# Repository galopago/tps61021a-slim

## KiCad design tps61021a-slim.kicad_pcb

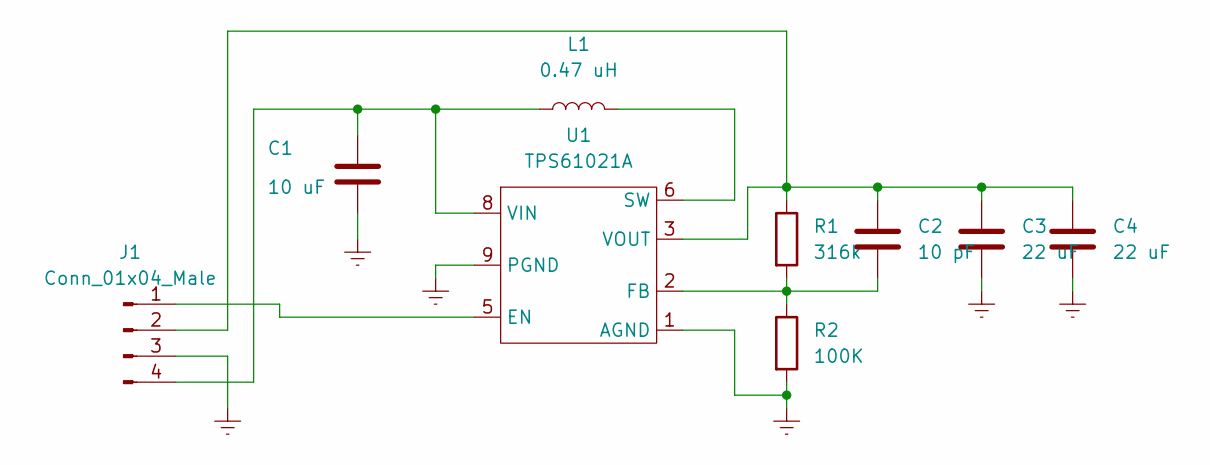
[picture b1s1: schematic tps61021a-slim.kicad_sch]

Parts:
C1: 10 uF; C_0805_2012Metric_Pad1.18x1.45mm_HandSolder
C2: 10 pF; C_0805_2012Metric_Pad1.18x1.45mm_HandSolder
C3, C4: 22 uF; C_0805_2012Metric_Pad1.18x1.45mm_HandSolder
J1: Conn_01x04_Male; PinHeader_1x04_P2.54mm_Vertical
L1: 0.47 uH; L_Ferrocore_DLG-0403
R1: 316k; R_0805_2012Metric_Pad1.20x1.40mm_HandSolder
R2: 100K; R_0805_2012Metric_Pad1.20x1.40mm_HandSolder
U1: TPS61021A; WSON-8-1EP_2x2mm_P0.5mm_EP0.9x1.6mm_ThermalVias

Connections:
Earth: C1.2, C3.2, C4.2, J1.3, R2.2, U1.1 (AGND), U1.9 (PGND)
unnamed: C1.1, J1.4, L1.1, U1.8 (VIN)
unnamed: C2.1, C3.1, C4.1, J1.2, R1.1, U1.3 (VOUT), U1.4 (VOUT)
unnamed: C2.2, R1.2, R2.1, U1.2 (FB)
unnamed: J1.1, U1.5 (EN)
unnamed: L1.2, U1.6 (SW), U1.7 (SW)

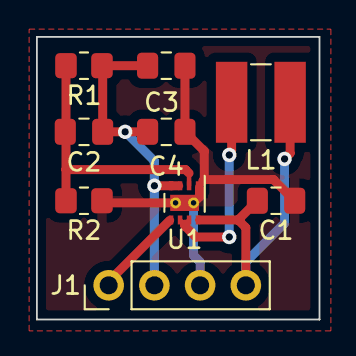
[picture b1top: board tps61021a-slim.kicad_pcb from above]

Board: 2 copper layers, 15.7 x 15.7 mm, 9 parts (0 on the bottom side), 6 nets.

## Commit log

2023-07-28 all components placed
2023-07-30 routed completed
2023-07-31 single board gerber
